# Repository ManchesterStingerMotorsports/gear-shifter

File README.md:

# Gear Shifter

ESP-IDF firmware and bench-test projects for the Manchester Stinger Motorsports electronic gear shifter controller.

The repository now contains four standalone ESP32-S3 projects:

```text
gear-shifter/
  production_firmware/             Production shifter firmware
  can_test_firmware/                Bench test: CAN/TWAI test scaffold
  button_test_firmware/            Bench test: buttons, LEDs, and low ESC torque
  encoder_position_test_firmware/  Bench test: print AMT20 encoder position
  Hardware/                        KiCad hardware files
  ESC Settings/                    ESC configuration files
  Archive Python Code/             Earlier prototype scripts
```

There is intentionally no ESP-IDF project at the repository root. Open/build one of the firmware folders directly.

## Production Firmware

Project folder:

```text
production_firmware/
```

Build:

```powershell
cd C:\Users\james\FS\gear-shifter\production_firmware
idf.py build
```

Flash:

```powershell
idf.py -p COMx flash monitor
```

Current behavior:

- starts the shifter task and a placeholder CAN task
- reads shift inputs from GPIO
- rejects shifts that would leave the valid gear range
- uses the latest CAN task output during pre-check: neutral position sensor first, then ECU gear when the car is moving
- checks the encoder before commanding the ESC
- commands the ESC for the requested shift after safety checks pass
- stops the ESC when the encoder reaches the calibrated target, an encoder read fails, or the shift timeout expires
- tracks the internal gear state through neutral, 1st, 2nd, 3rd, 4th, and 5th
- prints encoder position continuously while idle and during shift movement

Production pin, timing, and calibration constants live in:

```text
production_firmware/main/config.hpp
```

Production source layout:

```text
production_firmware/main/
  config.hpp
  main.cpp
  encoder/             AMT20 encoder driver
  esc/                 ESC PWM driver
  interrupts/          GPIO ISR/input latch code
  tasks/
    can_task/          CAN output placeholder/status
    shifter_task/      Main shifter control logic
```

Current values:

```cpp
static constexpr bool STANDALONE_TESTING = true;
static constexpr int8_t STANDALONE_INITIAL_GEAR = 2;
static constexpr float SHIFT_UP_TORQUE = 0.4f;
static constexpr float SHIFT_DOWN_TORQUE = -0.4f;
static constexpr float SHIFT_1_TO_NEUTRAL_TORQUE = SHIFT_UP_TORQUE;
static constexpr float SHIFT_NEUTRAL_TO_1_TORQUE = SHIFT_DOWN_TORQUE;
static constexpr uint16_t BASE_POSITION = 2840;
static constexpr uint16_t SHIFT_UP_STOP_POSITION = 2639;
static constexpr uint16_t SHIFT_DOWN_STOP_POSITION = 3039;
static constexpr uint16_t SHIFT_1_TO_NEUTRAL_STOP_POSITION = BASE_POSITION;
static constexpr uint16_t SHIFT_NEUTRAL_TO_1_STOP_POSITION = SHIFT_DOWN_STOP_POSITION;
static constexpr uint16_t SHIFT_POSITION_TOLERANCE = 20;
```

## Button And ESC Test

Project folder:

```text
button_test_firmware/
```

Behavior:

- reads UP, DOWN, and NEUTRAL as active-low inputs
- high impedance reads as released using the internal pull-up
- GND reads as pressed
- prints the button state to serial whenever it changes
- mirrors the debounced button states on the UP, DOWN, and NEUTRAL LEDs
- commands low positive ESC torque while UP is pressed
- commands low negative ESC torque while DOWN is pressed
- sends neutral ESC torque when neither or both shift directions are pressed

Constants live in:

```text
button_test_firmware/main/main.cpp
```

## Encoder Position Test

Project folder:

```text
encoder_position_test_firmware/
```

Behavior:

- repeatedly reads the AMT20 encoder over SPI
- prints the raw encoder position from `0` to `4095`

Constants live in:

```text
encoder_position_test_firmware/main/main.cpp
```

## CAN Test

Project folder:

```text
can_test_firmware/
```

Behavior:

- intentionally blank scaffold for CAN/TWAI bench testing
- builds with the same reusable `MSM_CAN` helper used by production firmware

Constants and test logic can be added in:

```text
can_test_firmware/main/main.cpp
```

## Pin Map

| Function | ESP32-S3 GPIO |
| --- | ---: |
| ESC PWM | GPIO 9 |
| Encoder CS | GPIO 10 |
| Encoder MOSI | GPIO 11 |
| Encoder SCLK | GPIO 12 |
| Encoder MISO | GPIO 13 |
| Shift up input | GPIO 48 |
| Shift down input | GPIO 45 |
| Shift neutral input | GPIO 47 |
| Shift up LED | GPIO 7 |
| Shift down LED | GPIO 6 |
| Shift neutral LED | GPIO 5 |
| CAN RX | GPIO 2 |
| CAN TX | GPIO 1 |

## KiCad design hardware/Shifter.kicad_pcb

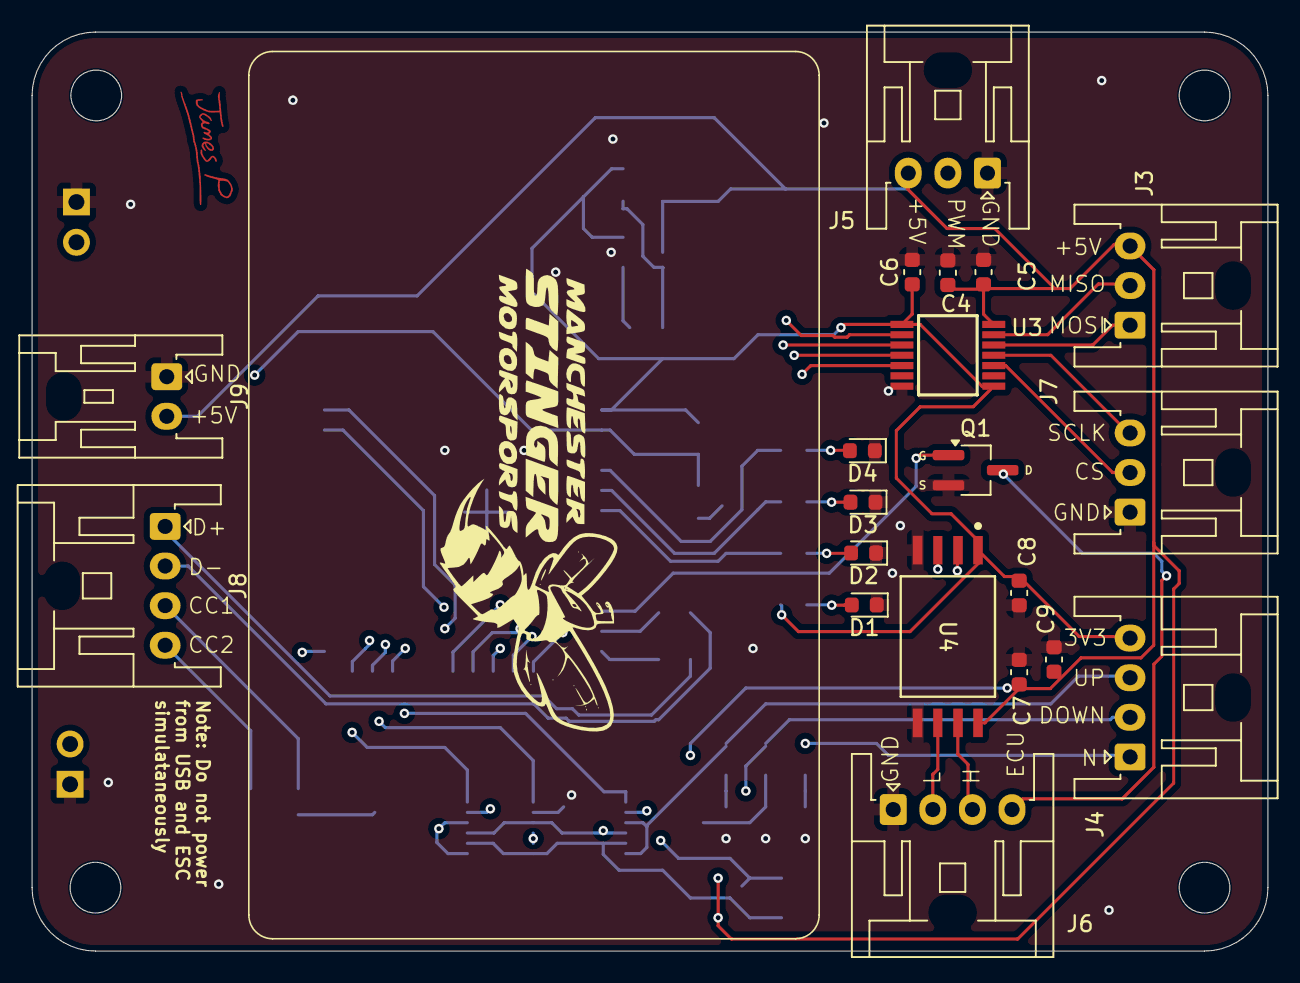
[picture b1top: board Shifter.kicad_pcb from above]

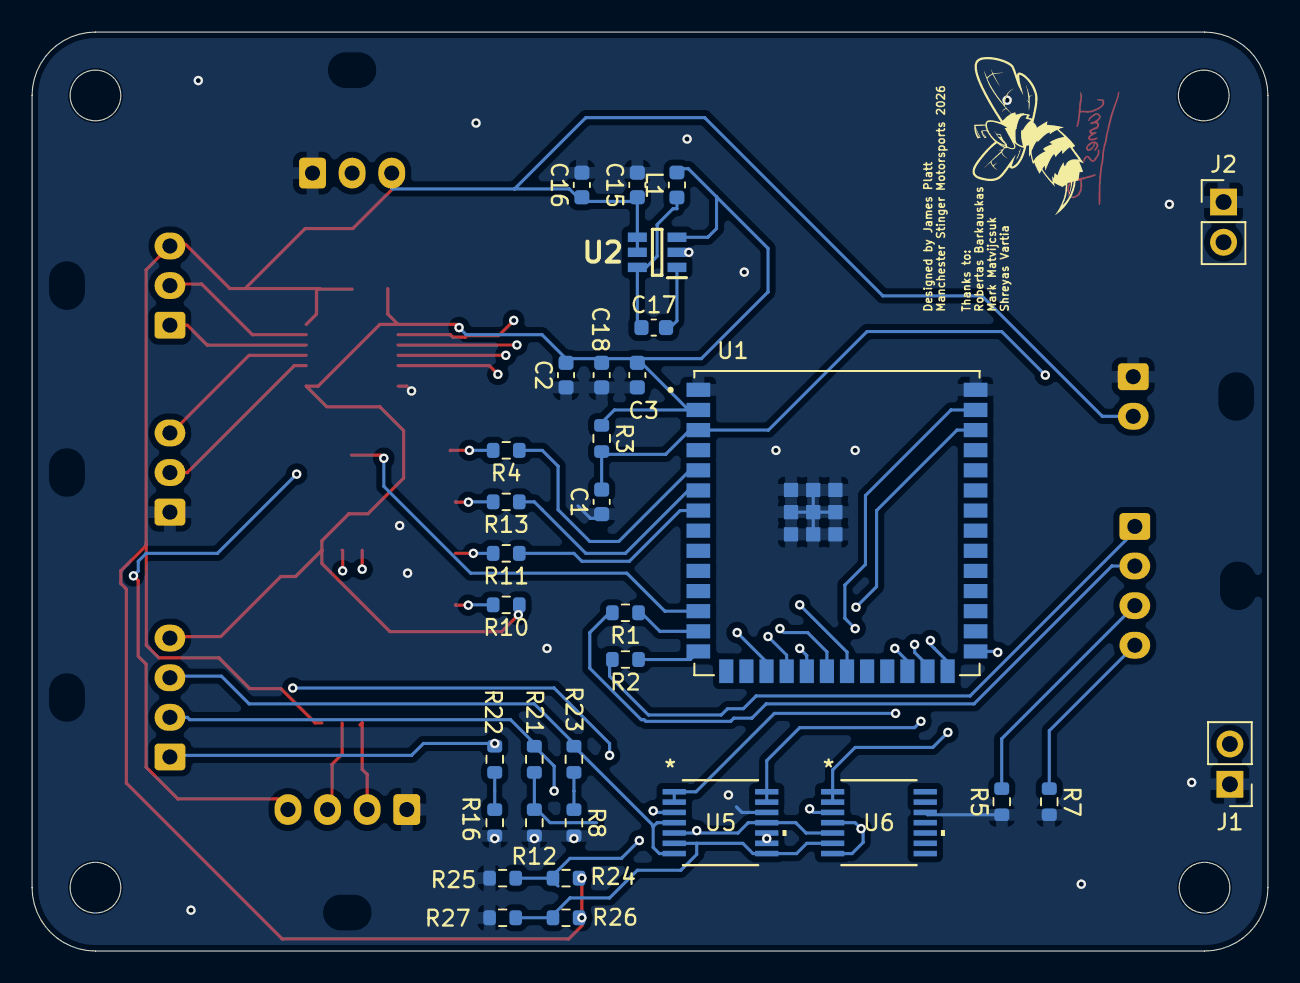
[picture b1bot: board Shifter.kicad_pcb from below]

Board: 4 copper layers, 78.0 x 58.0 mm, 53 parts (33 on the bottom side), 46 nets.

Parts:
C1, C5: 1u; C_0603_1608Metric
C2, C18: 10u; C_0603_1608Metric
C3, C4, C6, C7, C8: 0.1u; C_0603_1608Metric
C9: 4.7u; C_0603_1608Metric
C15: 2.2u; C_0603_1608Metric
C16, C17: 100n; C_0603_1608Metric
D1, D4: RED LED; LED_0603_1608Metric
D2: GREEN LED; LED_0603_1608Metric
D3: BLUE LED; LED_0603_1608Metric
J1: RST; PinHeader_1x02_P2.54mm_Vertical
J2: BSEL; PinHeader_1x02_P2.54mm_Vertical
J3, J5, J7: S03B-XASK-1; JST_XA_S03B-XASK-1_1x03_P2.50mm_Horizontal
J4, J6, J8: SO4B-XASK-1; JST_XA_S04B-XASK-1_1x04_P2.50mm_Horizontal
J9: Conn_01x02; JST_XA_S02B-XASK-1_1x02_P2.50mm_Horizontal
L1: 2.2u; L_0603_1608Metric
Q1: BSS205N; MOSFET_Single_SOT-23
R1, R2: 27; R_0603_1608Metric
R3, R8, R12, R16, R25, R27: 10k; R_0603_1608Metric
R4, R10: 270R; R_0603_1608Metric
R5, R7: 5k1; R_0603_1608Metric
R11: 220R; R_0603_1608Metric
R13: 100R; R_0603_1608Metric
R21, R22, R23: 180; R_0603_1608Metric
R24: 5k6; R_0603_1608Metric
R26: 12k; R_0603_1608Metric
U1: ESP32-S3-WROOM-1U-N4R2; XCVR_ESP32-S3-WROOM-1U-N4R2
U2: LMR50410Y3FQDBVRQ1; SOT95P280X145-6N
U3: MAX3390EEUD_T; SOP65P640X110-14N
U4: ISO1042BQDWVQ1; DWV0008A-MFG
U5, U6: TLV1704; PW14_TEX

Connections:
2.5V Ref: R26.2, R27.1, U5.6 (-), U5.8 (-), U6.6 (-)
3.5V Ref: R24.2, R25.1, U5.5 (+), U5.11 (+), U6.5 (+)
+3V3: C2.2, C3.2, C6.1, C8.2, C18.1, J4.4, L1.2, R3.1, R10.1, U1.2 (3V3), U2.3 (FB), U3.1 (VL), U3.8 (~THREE-STATE), U4.1 (VCC1)
+5V: C4.1, C5.1, C7.2, C9.2, C15.1, C16.1, J3.3, J5.3, J9.2, R24.1, R26.1, U2.4 (EN), U2.5 (VIN), U3.14 (VCC), U4.8 (VCC2), U5.3 (V+), U6.3 (V+)
CAND: U1.39 (IO1), U4.2 (TXD)
CANH: J6.3, U4.7 (CANH)
CANL: J6.2, U4.6 (CANL)
CANR: U1.38 (IO2), U4.3 (RXD)
CS: U1.18 (IO10), U3.5 (I_VL4)
DOWN: U1.25 (IO48), U5.13, U5.14
DOWN_LED: R13.1, U1.6 (IO6)
ECU: J6.4, Q1.3 (D)
E_CS: J7.2, U3.10 (O_VCC4)
E_MISO: J3.2, U3.13 (I_VCC1)
E_MOSI: J3.1, U3.12 (O_VCC2)
E_SCLK: J7.3, U3.11 (O_VCC3)
FLATSHIFT: Q1.1 (G), U1.12 (IO8)
GND: C1.1, C2.1, C3.1, C4.2, C5.2, C6.2, C7.1, C8.1, C9.1, C15.2, C16.2, C18.2, D1.1 (K), D2.1 (K), D3.1 (K), D4.1 (K), J1.1, J2.1, J5.1, J6.1, J7.1, J9.1, Q1.2 (S), R5.1, R7.2, R8.2, R12.2, R16.2, R25.2, R27.2, U1.1 (GND), U1.40 (GND__1), U1.41_1 (GND__2), U1.41_2 (GND__3), U1.41_3 (GND__4), U1.41_4 (GND__5), U1.41_5 (GND__6), U1.41_6 (GND__7), U1.41_7 (GND__8), U1.41_8 (GND__9), U1.41_9 (GND__10), U2.2 (GND), U3.7 (GND), U4.4 (GND1), U4.5 (GND2), U5.12 (V-), U6.12 (V-)
MISO: U1.21 (IO13), U3.2 (O_VL1)
MOSI: U1.19 (IO11), U3.3 (I_VL2)
Main_Reset: C1.2, J1.2, R3.2, U1.3 (EN)
NEUTRAL: U1.26 (IO45), U6.1, U6.2
NEUTRAL_LED: R4.1, U1.5 (IO5)
unnamed: D1.2 (A), R10.2
unnamed: D2.2 (A), R11.2
unnamed: D3.2 (A), R13.2
unnamed: D4.2 (A), R4.2
unnamed: J2.2, U1.27 (IO0)
unnamed: J8.3, R5.2
unnamed: J8.4, R7.1
unnamed: R1.1, U1.13 (IO19)
unnamed: R2.1, U1.14 (IO20)
unnamed: C17.2, U2.1 (CB)
unnamed: C17.1, L1.1, U2.6 (SW)
unnamed: R8.1, R23.2
unnamed: R12.1, R21.2
unnamed: R16.1, R22.2
PWM: J5.2, U1.17 (IO9)
SCLK: U1.20 (IO12), U3.4 (I_VL3)
SHIFT_DOWN: J4.2, R21.1, U5.9 (+), U5.10 (-)
SHIFT_NEUTRAL: J4.1, R22.1, U6.4 (-), U6.7 (+)
SHIFT_UP: J4.3, R23.1, U5.4 (-), U5.7 (+)
UP: U1.24 (IO47), U5.1, U5.2
UP_LED: R11.1, U1.7 (IO7)
USBD+: J8.1, R2.2
USBD-: J8.2, R1.2

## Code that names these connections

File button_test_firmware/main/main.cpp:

#include "ESC.hpp"

#include "driver/gpio.h"
#include "esp_err.h"
#include "esp_log.h"

#include "freertos/FreeRTOS.h"
#include "freertos/task.h"

static const char *TAG = "BUTTON_TEST";

static const gpio_num_t SHIFT_UP_GPIO = GPIO_NUM_48;
static const gpio_num_t SHIFT_DOWN_GPIO = GPIO_NUM_45;
static const gpio_num_t SHIFT_NEUTRAL_GPIO = GPIO_NUM_47;

static const gpio_num_t UP_LED_GPIO = GPIO_NUM_7;
static const gpio_num_t DOWN_LED_GPIO = GPIO_NUM_6;
static const gpio_num_t NEUTRAL_LED_GPIO = GPIO_NUM_5;

static const gpio_num_t ESC_PWM_GPIO = GPIO_NUM_9;

static constexpr uint32_t POLL_INTERVAL_MS = 20;
static constexpr uint32_t DEBOUNCE_MS = 60;
static constexpr float DOWN_TEST_TORQUE = -0.15f;
static constexpr bool LED_ACTIVE_HIGH = true;

static constexpr uint64_t gpio_select(gpio_num_t gpio)
{
    return 1ULL << static_cast<uint64_t>(gpio);
}

struct ButtonState
{
    bool up;
    bool down;
    bool neutral;
};

static void setup_inputs()
{
    gpio_config_t input_config = {};
    input_config.pin_bit_mask =
        gpio_select(SHIFT_DOWN_GPIO) |
        gpio_select(SHIFT_NEUTRAL_GPIO);
    input_config.mode = GPIO_MODE_INPUT;
    input_config.pull_up_en = GPIO_PULLUP_ENABLE;
    input_config.pull_down_en = GPIO_PULLDOWN_DISABLE;
    input_config.intr_type = GPIO_INTR_DISABLE;

    ESP_ERROR_CHECK(gpio_config(&input_config));
}

static void setup_outputs()
{
    gpio_config_t output_config = {};
    output_config.pin_bit_mask =
        gpio_select(UP_LED_GPIO) |
        gpio_select(DOWN_LED_GPIO) |
        gpio_select(NEUTRAL_LED_GPIO);
    output_config.mode = GPIO_MODE_OUTPUT;
    output_config.pull_up_en = GPIO_PULLUP_DISABLE;
    output_config.pull_down_en = GPIO_PULLDOWN_DISABLE;
    output_config.intr_type = GPIO_INTR_DISABLE;

    ESP_ERROR_CHECK(gpio_config(&output_config));

    const int off_level = LED_ACTIVE_HIGH ? 0 : 1;
    ESP_ERROR_CHECK(gpio_set_level(UP_LED_GPIO, off_level));
    ESP_ERROR_CHECK(gpio_set_level(DOWN_LED_GPIO, off_level));
    ESP_ERROR_CHECK(gpio_set_level(NEUTRAL_LED_GPIO, off_level));
}

static bool button_pressed(gpio_num_t gpio)
{
    return gpio_get_level(gpio) == 0;
}

static void set_led(gpio_num_t gpio, bool on)
{
    const bool level = LED_ACTIVE_HIGH ? on : !on;
    ESP_ERROR_CHECK(gpio_set_level(gpio, level ? 1 : 0));
}

static void set_leds(const ButtonState &state)
{
    set_led(UP_LED_GPIO, false);
    set_led(DOWN_LED_GPIO, state.down);
    set_led(NEUTRAL_LED_GPIO, state.neutral);
}

static float torque_for_buttons(const ButtonState &state)
{
    if (state.down)
    {
        return DOWN_TEST_TORQUE;
    }

    return 0.0f;
}

static void set_esc_from_buttons(ESC &esc, const ButtonState &state)
{
    esc.set_torque(torque_for_buttons(state));
}

static ButtonState read_buttons()
{
    return {
        false,
        button_pressed(SHIFT_DOWN_GPIO),
        button_pressed(SHIFT_NEUTRAL_GPIO),
    };
}

static bool states_differ(const ButtonState &left, const ButtonState &right)
{
    return left.up != right.up ||
           left.down != right.down ||
           left.neutral != right.neutral;
}

static void log_buttons(const ButtonState &state)
{
    ESP_LOGI(TAG,
             "UP=%s DOWN=%s NEUTRAL=%s",
             state.up ? "PRESSED" : "released",
             state.down ? "PRESSED" : "released",
             state.neutral ? "PRESSED" : "released");
}

extern "C" void app_main(void)
{
    ESP_LOGI(TAG, "Button and ESC test started");
    ESP_LOGI(TAG,
             "Active-low inputs: DOWN GPIO=%d, NEUTRAL GPIO=%d; UP disabled",
             static_cast<int>(SHIFT_DOWN_GPIO),
             static_cast<int>(SHIFT_NEUTRAL_GPIO));
    ESP_LOGI(TAG,
             "LED outputs: UP GPIO=%d, DOWN GPIO=%d, NEUTRAL GPIO=%d",
             static_cast<int>(UP_LED_GPIO),
             static_cast<int>(DOWN_LED_GPIO),
             static_cast<int>(NEUTRAL_LED_GPIO));
    ESP_LOGI(TAG,
             "ESC PWM GPIO=%d, DOWN torque=%d/1000; UP torque disabled",
             static_cast<int>(ESC_PWM_GPIO),
             static_cast<int>(DOWN_TEST_TORQUE * 1000.0f));

    setup_outputs();
    setup_inputs();

    ESC esc(ESC_PWM_GPIO);

    ButtonState debounced_state = read_buttons();
    ButtonState candidate_state = debounced_state;
    uint32_t candidate_ticks = 0;

    set_leds(debounced_state);
    set_esc_from_buttons(esc, debounced_state);
    log_buttons(debounced_state);

    for (;;)
    {
        const ButtonState state = read_buttons();
        if (states_differ(state, candidate_state))
        {
            candidate_state = state;
            candidate_ticks = 0;
        }
        else if (states_differ(candidate_state, debounced_state))
        {
            candidate_ticks += POLL_INTERVAL_MS;
            if (candidate_ticks >= DEBOUNCE_MS)
            {
                debounced_state = candidate_state;
                candidate_ticks = 0;
                set_leds(debounced_state);
                set_esc_from_buttons(esc, debounced_state);
                log_buttons(debounced_state);
            }
        }

        vTaskDelay(pdMS_TO_TICKS(POLL_INTERVAL_MS));
    }
}

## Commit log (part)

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2025-11-03 Add Shifter Kicad Schem
    Added USB-C, Linear Batt->5V reg, Switching 5V->3V3 reg
2025-11-03 Add Gear shifter code
    Duplicated from the sharepoint
2025-11-14 Create .gitignore for KiCad project files
    Added a .gitignore file to exclude KiCad temporary and backup files.
2025-11-15 Update Schematic
    Adds ESP32, CAN and basically everything...
2025-11-16 route it all and make minor schem mods
2025-11-19 Add SCS checks to Schematic and PCB
2026-04-15 Add ESP framework
2026-04-15 Add latest MSM_CAN
2026-04-15 Refactor tasks
2026-04-15 code to spin off shift and CAN tasks
2026-04-15 add hardware
2026-04-15 configure ISRs
2026-04-16 Setup ISR framework
2026-04-17 ESC class
2026-04-18 update MSM_CAN to latest ver
2026-04-18 add encoder stuff
2026-04-18 make it compile
2026-04-18 Fix multithreading weirdness
2026-04-18 ecu gear count takes priority
2026-04-18 minor changes
2026-04-19 better comments
2026-04-30 fix everything
2026-05-26 rob-proofing
2026-06-06 refactor and add can task WIP
2026-06-06 adds ifdef for standalone testing
2026-06-09 ready to go
2026-06-09 actually good to go
2026-06-10 can task beginnings
2026-06-10 can task
2026-06-11 add multithreading (blazingly fast)
2026-06-11 can test firmware environment
